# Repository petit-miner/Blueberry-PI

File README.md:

Blueberry PI

I have designed this PCB, because the sheer power of this SoC, at very low power consumption, combined with its display capabilities, it offers options that makers have never seen before.<br> 
<br>
There are two versions available: the 2 layer and 4 layer version.<br> 
Have a look at the subfolder for the 2 and 4 layer version to check out the specific features.<br>
<br>
<br>
The Blueberry PI:<br>
• SoC Allwinner V3s:<br>
	- ARM Cortex-A7 @ 1.2GHz<br>
	- 64 Megabyte of RAM<br>
•	10 / 100M Ethernet <br>
•	Wifi and Bluetooth (RTL8723BS)  <br>
•	1 USB Host Port / 1 micro USB port <br> 
•	MIPI CSI interface<br>
•	pinheader for an OV2640 and an OV7670 parallel camera<br>
•	parallel RGB interface, compatible with 40pin parallel RGB displays<br>
•	audio jack (3,5mm)<br>
•	onboard microphone<br>
•	a 26pin Raspberry PI compatible header<br>
•	SPI Flash <br>
•	SD card slot<br>

The Blueberry PI can boot from an SD card or SPI Flash. <br>
I'm currently <b> not </B> available for custom projects. <br>
If you have any questions email me at info.blueberrypi@gmail.com <br>

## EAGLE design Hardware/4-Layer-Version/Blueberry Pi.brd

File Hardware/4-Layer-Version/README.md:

Hardware

This is the 4 Layer version of the Blueberry PI. It has a richer featureset than the 2 Layer PCB.<br>
Keep in mind that this PCB isn' tested yet, I will keep you updated.<br>
It has the following features:<br>
<br>
• SoC Allwinner V3s:<br>
• ARM Cortex-A7 @ 1.2GHz<br>
• 64 Megabyte of RAM<br>
• Ethernet Jack<br>
• Wifi and Bluetooth (RTL8723BS)<br>
• 1 USB Host Port / 1 micro USB port<br>
• MIPI CSI interface, pin compatible with the Raspberry Pi camera<br>
• pinheader for an OV2640 and an OV7670 parallel camera<br>
• parallel RGB interface, compatible with 40pin parallel RGB displays<br>
• VGA Output<br>
• HDMI Input with the ADV7611 1080p @ 30 fps<br>
• Audio jack (3,5mm)<br>
• onboard microphone<br>
• a 26pin Raspberry PI compatible header<br>
• SPI Flash<br>
• SD card slot <br>
<br>

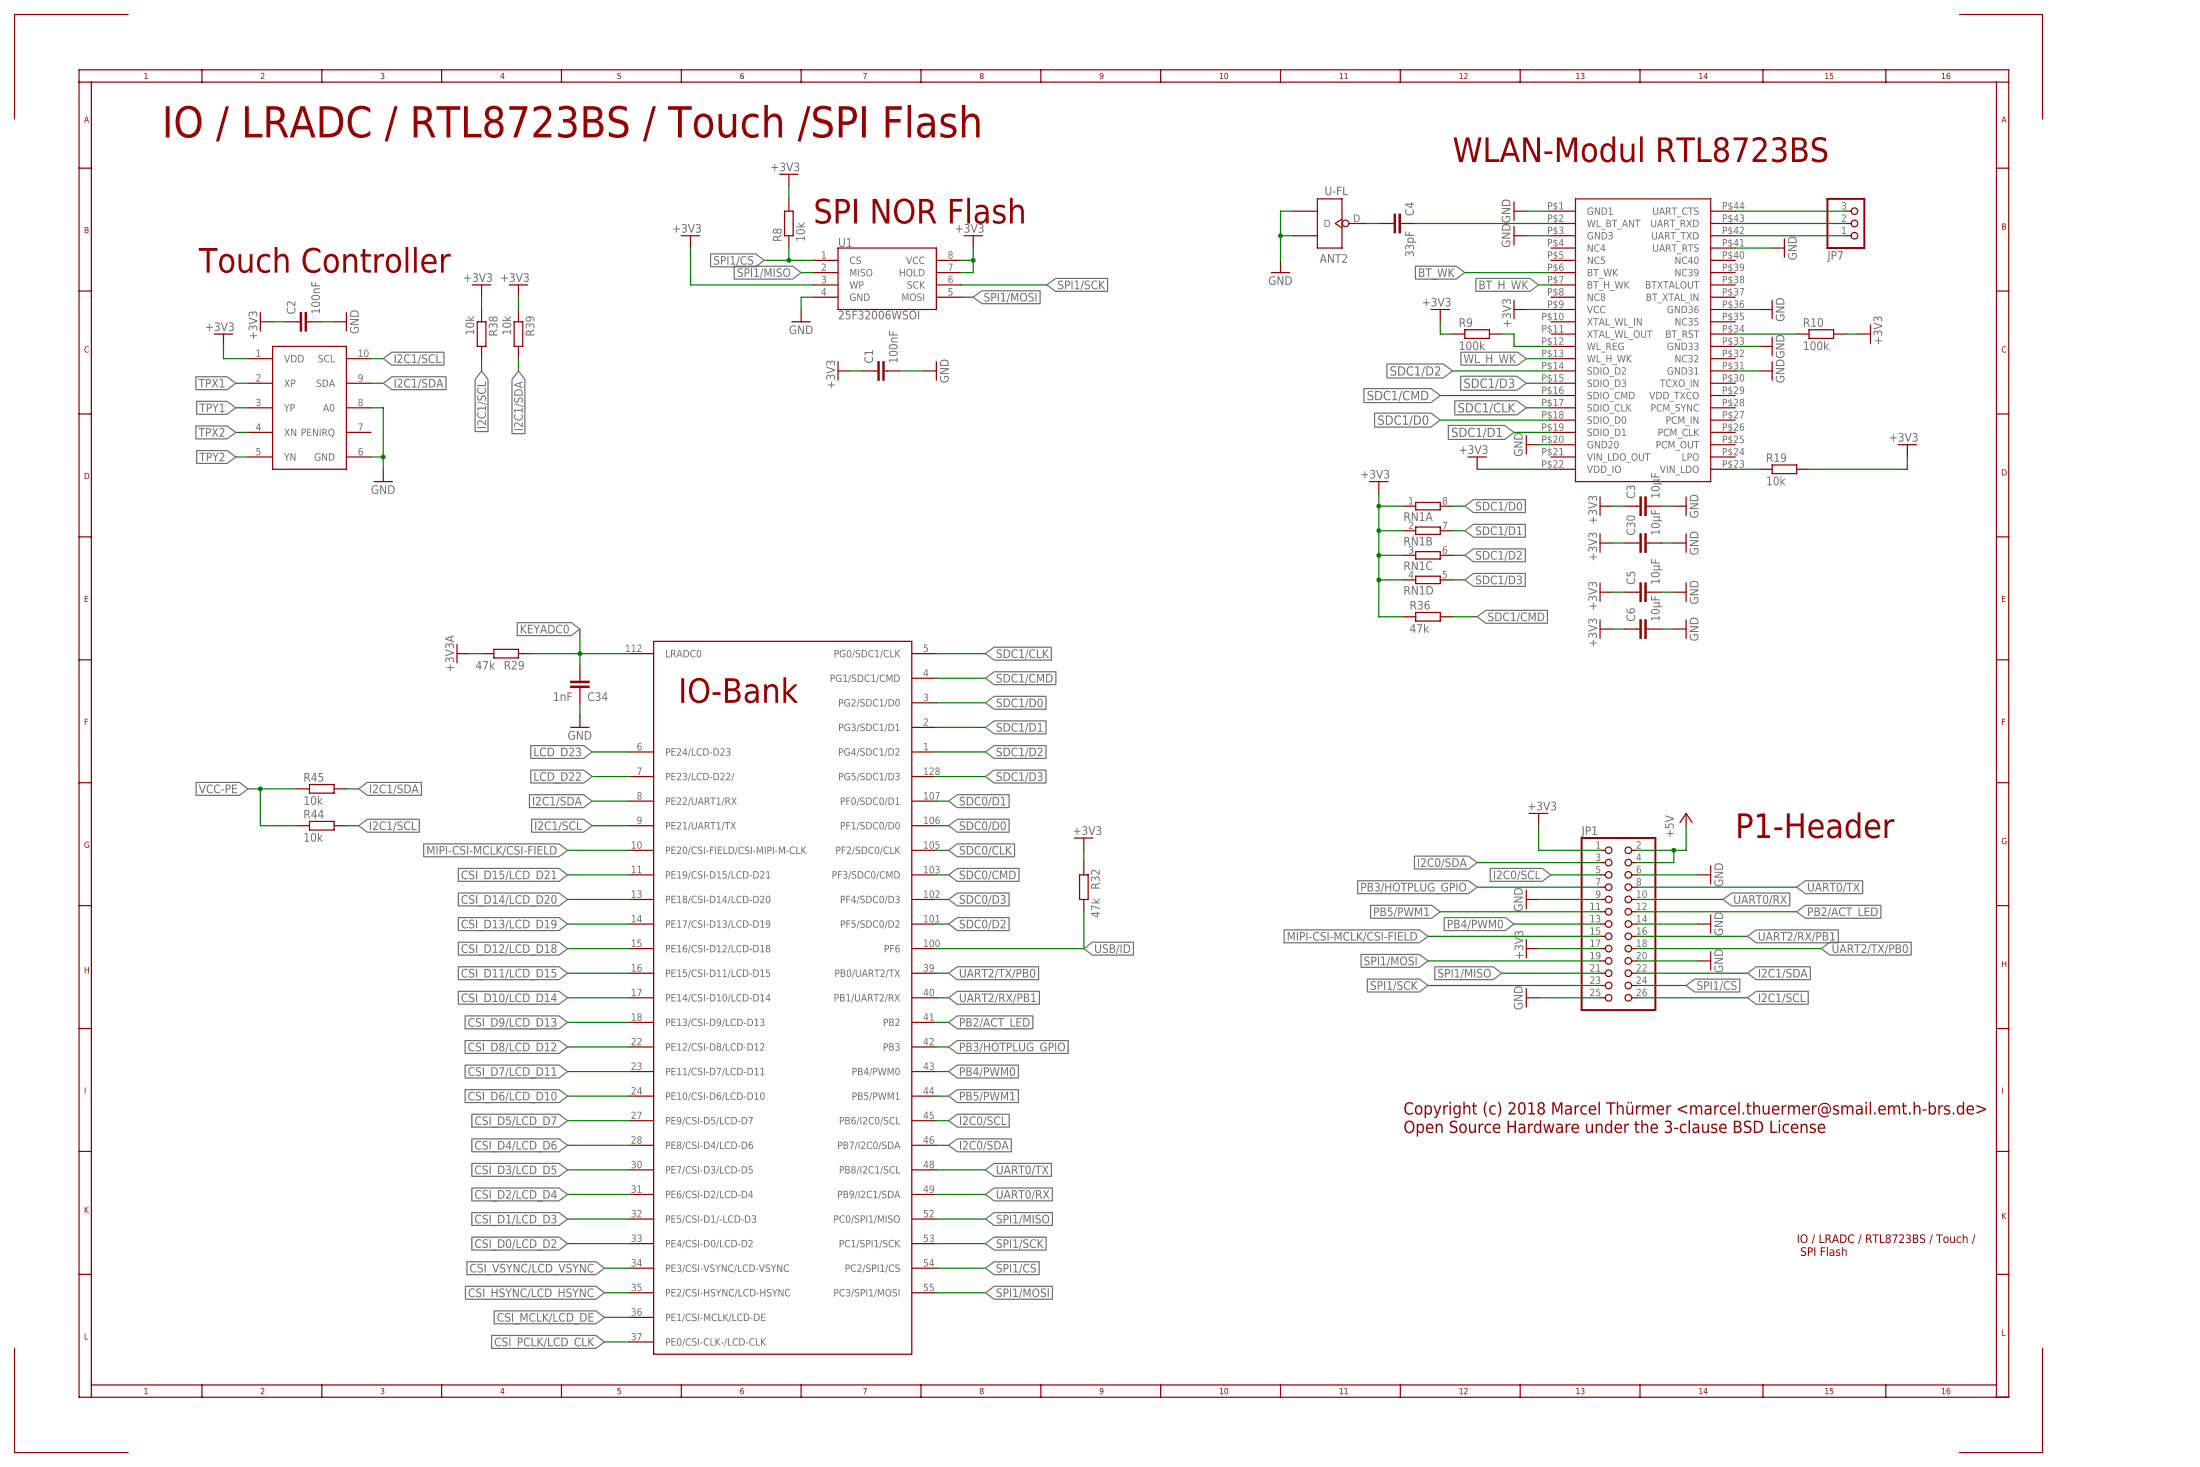
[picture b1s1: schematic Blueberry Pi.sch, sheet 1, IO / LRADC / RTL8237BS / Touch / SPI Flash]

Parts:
ANT2: U-FL; U-FL3P-SMD-2.6X2.6X1.0MM
C1, C2: 100nF; C0603
C3, C5, C6, C30: 10µF; C0805
C4: 33pF; C0603
C34: 1nF; C0603
JP1: PINHD-2X13; 2X13
JP7: PINHD-1X3M; 1X03M
R8, R19, R38, R39, R44, R45: 10k; R0603
R9, R10: 100k; R0603
R29, R32, R36: 47k; R0603
RN1: 4R-NEXB38V; EXB38V
U1: 25F32006WSOI; SO08-EIAJ
U$1: V3S; QFP-128
U$2: RTL8723BS; LGA
U$8: NS2009; MSOP10

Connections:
+3V3: C1.1, C2.1, C3.1, C5.1, C6.1, C30.1, JP1.1, JP1.17, R8.2, R9.1, R10.2, R19.2, R32.1, R36.1, R38.1, R39.1, RN1.1, RN1.2 (1), RN1.3 (1), RN1.4 (1), U1.3 (WP), U1.7 (HOLD), U1.8 (VCC), U$2.P$9 (VCC), U$2.P$22 (VDD_IO), U$8.1 (VDD); also elsewhere on the board
+3V3A: R29.2; also elsewhere on the board
+5V: JP1.2, JP1.4; also elsewhere on the board
BT_H_WK: U$2.P$7 (BT_H_WK)
BT_WK: U$2.P$6 (BT_WK)
CSI_D0/LCD_D2: U$1.33 (PE4/CSI-D0/LCD-D2); also elsewhere on the board
CSI_D1/LCD_D3: U$1.32 (PE5/CSI-D1/-LCD-D3); also elsewhere on the board
CSI_D2/LCD_D4: U$1.31 (PE6/CSI-D2/LCD-D4); also elsewhere on the board
CSI_D3/LCD_D5: U$1.30 (PE7/CSI-D3/LCD-D5); also elsewhere on the board
CSI_D4/LCD_D6: U$1.28 (PE8/CSI-D4/LCD-D6); also elsewhere on the board
CSI_D5/LCD_D7: U$1.27 (PE9/CSI-D5/LCD-D7); also elsewhere on the board
CSI_D6/LCD_D10: U$1.24 (PE10/CSI-D6/LCD-D10); also elsewhere on the board
CSI_D7/LCD_D11: U$1.23 (PE11/CSI-D7/LCD-D11); also elsewhere on the board
CSI_D8/LCD_D12: U$1.22 (PE12/CSI-D8/LCD-D12); also elsewhere on the board
CSI_D9/LCD_D13: U$1.18 (PE13/CSI-D9/LCD-D13); also elsewhere on the board
CSI_D10/LCD_D14: U$1.17 (PE14/CSI-D10/LCD-D14); also elsewhere on the board
CSI_D11/LCD_D15: U$1.16 (PE15/CSI-D11/LCD-D15); also elsewhere on the board
CSI_D12/LCD_D18: U$1.15 (PE16/CSI-D12/LCD-D18); also elsewhere on the board
CSI_D13/LCD_D19: U$1.14 (PE17/CSI-D13/LCD-D19); also elsewhere on the board
CSI_D14/LCD_D20: U$1.13 (PE18/CSI-D14/LCD-D20); also elsewhere on the board
CSI_D15/LCD_D21: U$1.11 (PE19/CSI-D15/LCD-D21); also elsewhere on the board
CSI_HSYNC/LCD_HSYNC: U$1.35 (PE2/CSI-HSYNC/LCD-HSYNC); also elsewhere on the board
CSI_MCLK/LCD_DE: U$1.36 (PE1/CSI-MCLK/LCD-DE); also elsewhere on the board
CSI_PCLK/LCD_CLK: U$1.37 (PE0/CSI-CLK-/LCD-CLK); also elsewhere on the board
CSI_VSYNC/LCD_VSYNC: U$1.34 (PE3/CSI-VSYNC/LCD-VSYNC); also elsewhere on the board
GND: ANT2.GND1, ANT2.GND2, C1.2, C2.2, C3.2, C5.2, C6.2, C30.2, C34.1, JP1.6, JP1.9, JP1.14, JP1.20, JP1.25, U1.4 (GND), U$2.P$1 (GND1), U$2.P$3 (GND3), U$2.P$20 (GND20), U$2.P$31 (GND31), U$2.P$33 (GND33), U$2.P$36 (GND36), U$2.P$41 (UART_RTS), U$8.6 (GND), U$8.8 (A0); also elsewhere on the board
I2C0/SCL: JP1.5, U$1.45 (PB6/I2C0/SCL)
I2C0/SDA: JP1.3, U$1.46 (PB7/I2C0/SDA)
I2C1/SCL: JP1.26, R38.2, R44.2, U$1.9 (PE21/UART1/TX), U$8.10 (SCL); also elsewhere on the board
I2C1/SDA: JP1.22, R39.2, R45.2, U$1.8 (PE22/UART1/RX), U$8.9 (SDA); also elsewhere on the board
KEYADC0: C34.2, R29.1, U$1.112 (LRADC0)
LCD_D22: U$1.7 (PE23/LCD-D22/); also elsewhere on the board
LCD_D23: U$1.6 (PE24/LCD-D23); also elsewhere on the board
MIPI-CSI-MCLK/CSI-FIELD: JP1.15, U$1.10 (PE20/CSI-FIELD/CSI-MIPI-M-CLK); also elsewhere on the board
unnamed: ANT2.D, C4.2
unnamed: R19.1, U$2.P$23 (VIN_LDO)
unnamed: JP7.3, U$2.P$44 (UART_CTS)
unnamed: R9.2, U$2.P$12 (WL_REG)
unnamed: JP7.2, U$2.P$43 (UART_RXD)
unnamed: JP7.1, U$2.P$42 (UART_TXD)
unnamed: R10.1, U$2.P$34 (BT_RST)
unnamed: C4.1, U$2.P$2 (WL_BT_ANT)
PB2/ACT_LED: JP1.12, U$1.41 (PB2); also elsewhere on the board
PB3/HOTPLUG_GPIO: JP1.7, U$1.42 (PB3); also elsewhere on the board
PB4/PWM0: JP1.13, U$1.43 (PB4/PWM0)
PB5/PWM1: JP1.11, U$1.44 (PB5/PWM1)
SDC0/CLK: U$1.105 (PF2/SDC0/CLK); also elsewhere on the board
SDC0/CMD: U$1.103 (PF3/SDC0/CMD); also elsewhere on the board
SDC0/D0: U$1.106 (PF1/SDC0/D0); also elsewhere on the board
SDC0/D1: U$1.107 (PF0/SDC0/D1); also elsewhere on the board
SDC0/D2: U$1.101 (PF5/SDC0/D2); also elsewhere on the board
SDC0/D3: U$1.102 (PF4/SDC0/D3); also elsewhere on the board
SDC1/CLK: U$1.5 (PG0/SDC1/CLK), U$2.P$17 (SDIO_CLK)
SDC1/CMD: R36.2, U$1.4 (PG1/SDC1/CMD), U$2.P$16 (SDIO_CMD)
SDC1/D0: RN1.8 (2), U$1.3 (PG2/SDC1/D0), U$2.P$18 (SDIO_D0)
SDC1/D1: RN1.7 (2), U$1.2 (PG3/SDC1/D1), U$2.P$19 (SDIO_D1)
SDC1/D2: RN1.6 (2), U$1.1 (PG4/SDC1/D2), U$2.P$14 (SDIO_D2)
SDC1/D3: RN1.5 (2), U$1.128 (PG5/SDC1/D3), U$2.P$15 (SDIO_D3)
SPI1/CS: JP1.24, R8.1, U1.1 (CS), U$1.54 (PC2/SPI1/CS)
SPI1/MISO: JP1.21, U1.2 (MISO), U$1.52 (PC0/SPI1/MISO)
SPI1/MOSI: JP1.19, U1.5 (MOSI), U$1.55 (PC3/SPI1/MOSI)
SPI1/SCK: JP1.23, U1.6 (SCK), U$1.53 (PC1/SPI1/SCK)
TPX1: U$8.2 (XP); also elsewhere on the board
TPX2: U$8.4 (XN); also elsewhere on the board
TPY1: U$8.3 (YP); also elsewhere on the board
TPY2: U$8.5 (YN); also elsewhere on the board
UART0/RX: JP1.10, U$1.49 (PB9/I2C1/SDA)
UART0/TX: JP1.8, U$1.48 (PB8/I2C1/SCL)
UART2/RX/PB1: JP1.16, U$1.40 (PB1/UART2/RX)
UART2/TX/PB0: JP1.18, U$1.39 (PB0/UART2/TX)
USB/ID: R32.2, U$1.100 (PF6); also elsewhere on the board
VCC-PE: R44.1, R45.1; also elsewhere on the board
WL_H_WK: U$2.P$13 (WL_H_WK)

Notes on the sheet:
IO / LRADC / RTL8723BS / Touch / SPI Flash
Copyright (c) 2018 Marcel Thürmer <marcel.thuermer@smail.emt.h-brs.de> Open Source Hardware under the 3-clause BSD License
SPI NOR Flash
WLAN-Modul RTL8723BS
P1-Header
Touch Controller
IO / LRADC / RTL8723BS / Touch /SPI Flash

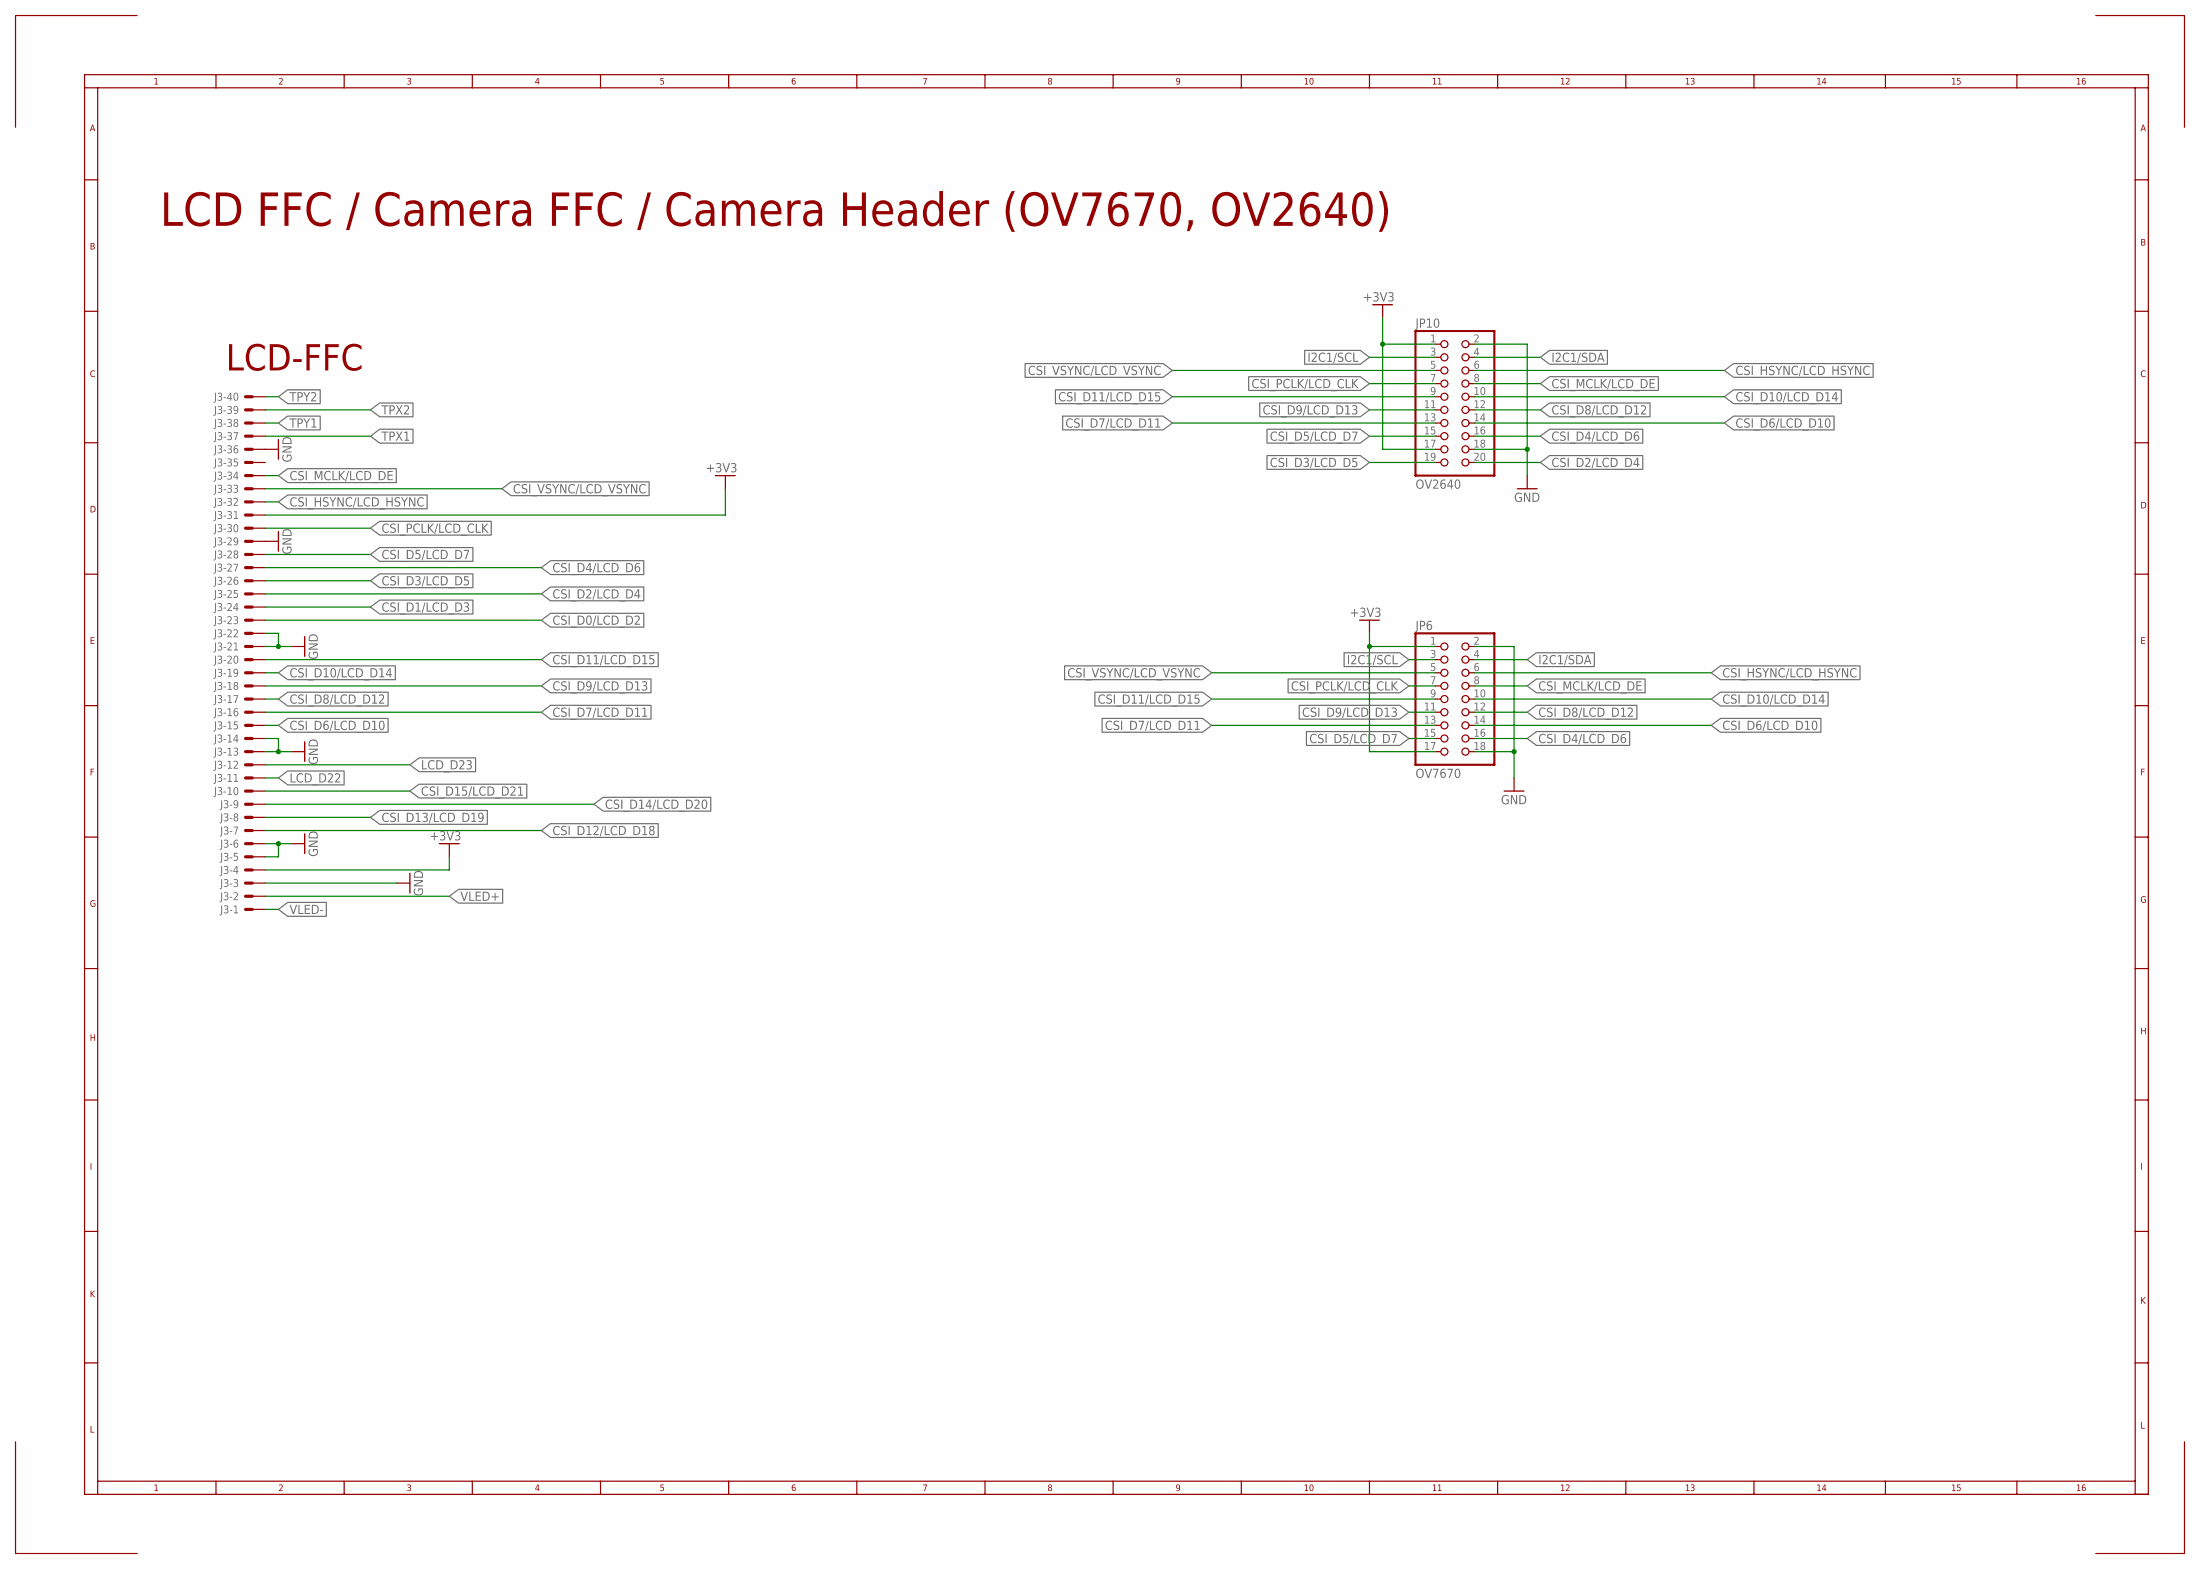
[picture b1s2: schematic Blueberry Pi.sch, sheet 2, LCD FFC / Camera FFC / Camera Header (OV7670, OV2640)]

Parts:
J3: 40PINFPCH15-1LW; XF2H-4015-1LW
JP6: OV7670; 2X09
JP10: OV2640; 2X10

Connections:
+3V3: J3.4 (MS), J3.31 (MS), JP6.1, JP6.17, JP10.1, JP10.17; also elsewhere on the board
CSI_D0/LCD_D2: J3.23 (MS); also elsewhere on the board
CSI_D1/LCD_D3: J3.24 (MS); also elsewhere on the board
CSI_D2/LCD_D4: J3.25 (MS), JP10.20; also elsewhere on the board
CSI_D3/LCD_D5: J3.26 (MS), JP10.19; also elsewhere on the board
CSI_D4/LCD_D6: J3.27 (MS), JP6.16, JP10.16; also elsewhere on the board
CSI_D5/LCD_D7: J3.28 (MS), JP6.15, JP10.15; also elsewhere on the board
CSI_D6/LCD_D10: J3.15 (MS), JP6.14, JP10.14; also elsewhere on the board
CSI_D7/LCD_D11: J3.16 (MS), JP6.13, JP10.13; also elsewhere on the board
CSI_D8/LCD_D12: J3.17 (MS), JP6.12, JP10.12; also elsewhere on the board
CSI_D9/LCD_D13: J3.18 (MS), JP6.11, JP10.11; also elsewhere on the board
CSI_D10/LCD_D14: J3.19 (MS), JP6.10, JP10.10; also elsewhere on the board
CSI_D11/LCD_D15: J3.20 (MS), JP6.9, JP10.9; also elsewhere on the board
CSI_D12/LCD_D18: J3.7 (MS); also elsewhere on the board
CSI_D13/LCD_D19: J3.8 (MS); also elsewhere on the board
CSI_D14/LCD_D20: J3.9 (MS); also elsewhere on the board
CSI_D15/LCD_D21: J3.10 (MS); also elsewhere on the board
CSI_HSYNC/LCD_HSYNC: J3.32 (MS), JP6.6, JP10.6; also elsewhere on the board
CSI_MCLK/LCD_DE: J3.34 (MS), JP6.8, JP10.8; also elsewhere on the board
CSI_PCLK/LCD_CLK: J3.30 (MS), JP6.7, JP10.7; also elsewhere on the board
CSI_VSYNC/LCD_VSYNC: J3.33 (MS), JP6.5, JP10.5; also elsewhere on the board
GND: J3.3 (MS), J3.5 (MS), J3.6 (MS), J3.13 (MS), J3.14 (MS), J3.21 (MS), J3.22 (MS), J3.29 (MS), J3.36 (MS), JP6.2, JP6.18, JP10.2, JP10.18; also elsewhere on the board
I2C1/SCL: JP6.3, JP10.3; also elsewhere on the board
I2C1/SDA: JP6.4, JP10.4; also elsewhere on the board
LCD_D22: J3.11 (MS); also elsewhere on the board
LCD_D23: J3.12 (MS); also elsewhere on the board
TPX1: J3.37 (MS); also elsewhere on the board
TPX2: J3.39 (MS); also elsewhere on the board
TPY1: J3.38 (MS); also elsewhere on the board
TPY2: J3.40 (MS); also elsewhere on the board
VLED+: J3.2 (MS); also elsewhere on the board
VLED-: J3.1 (MSV); also elsewhere on the board

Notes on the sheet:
LCD-FFC
LCD FFC / Camera FFC / Camera Header (OV7670, OV2640)

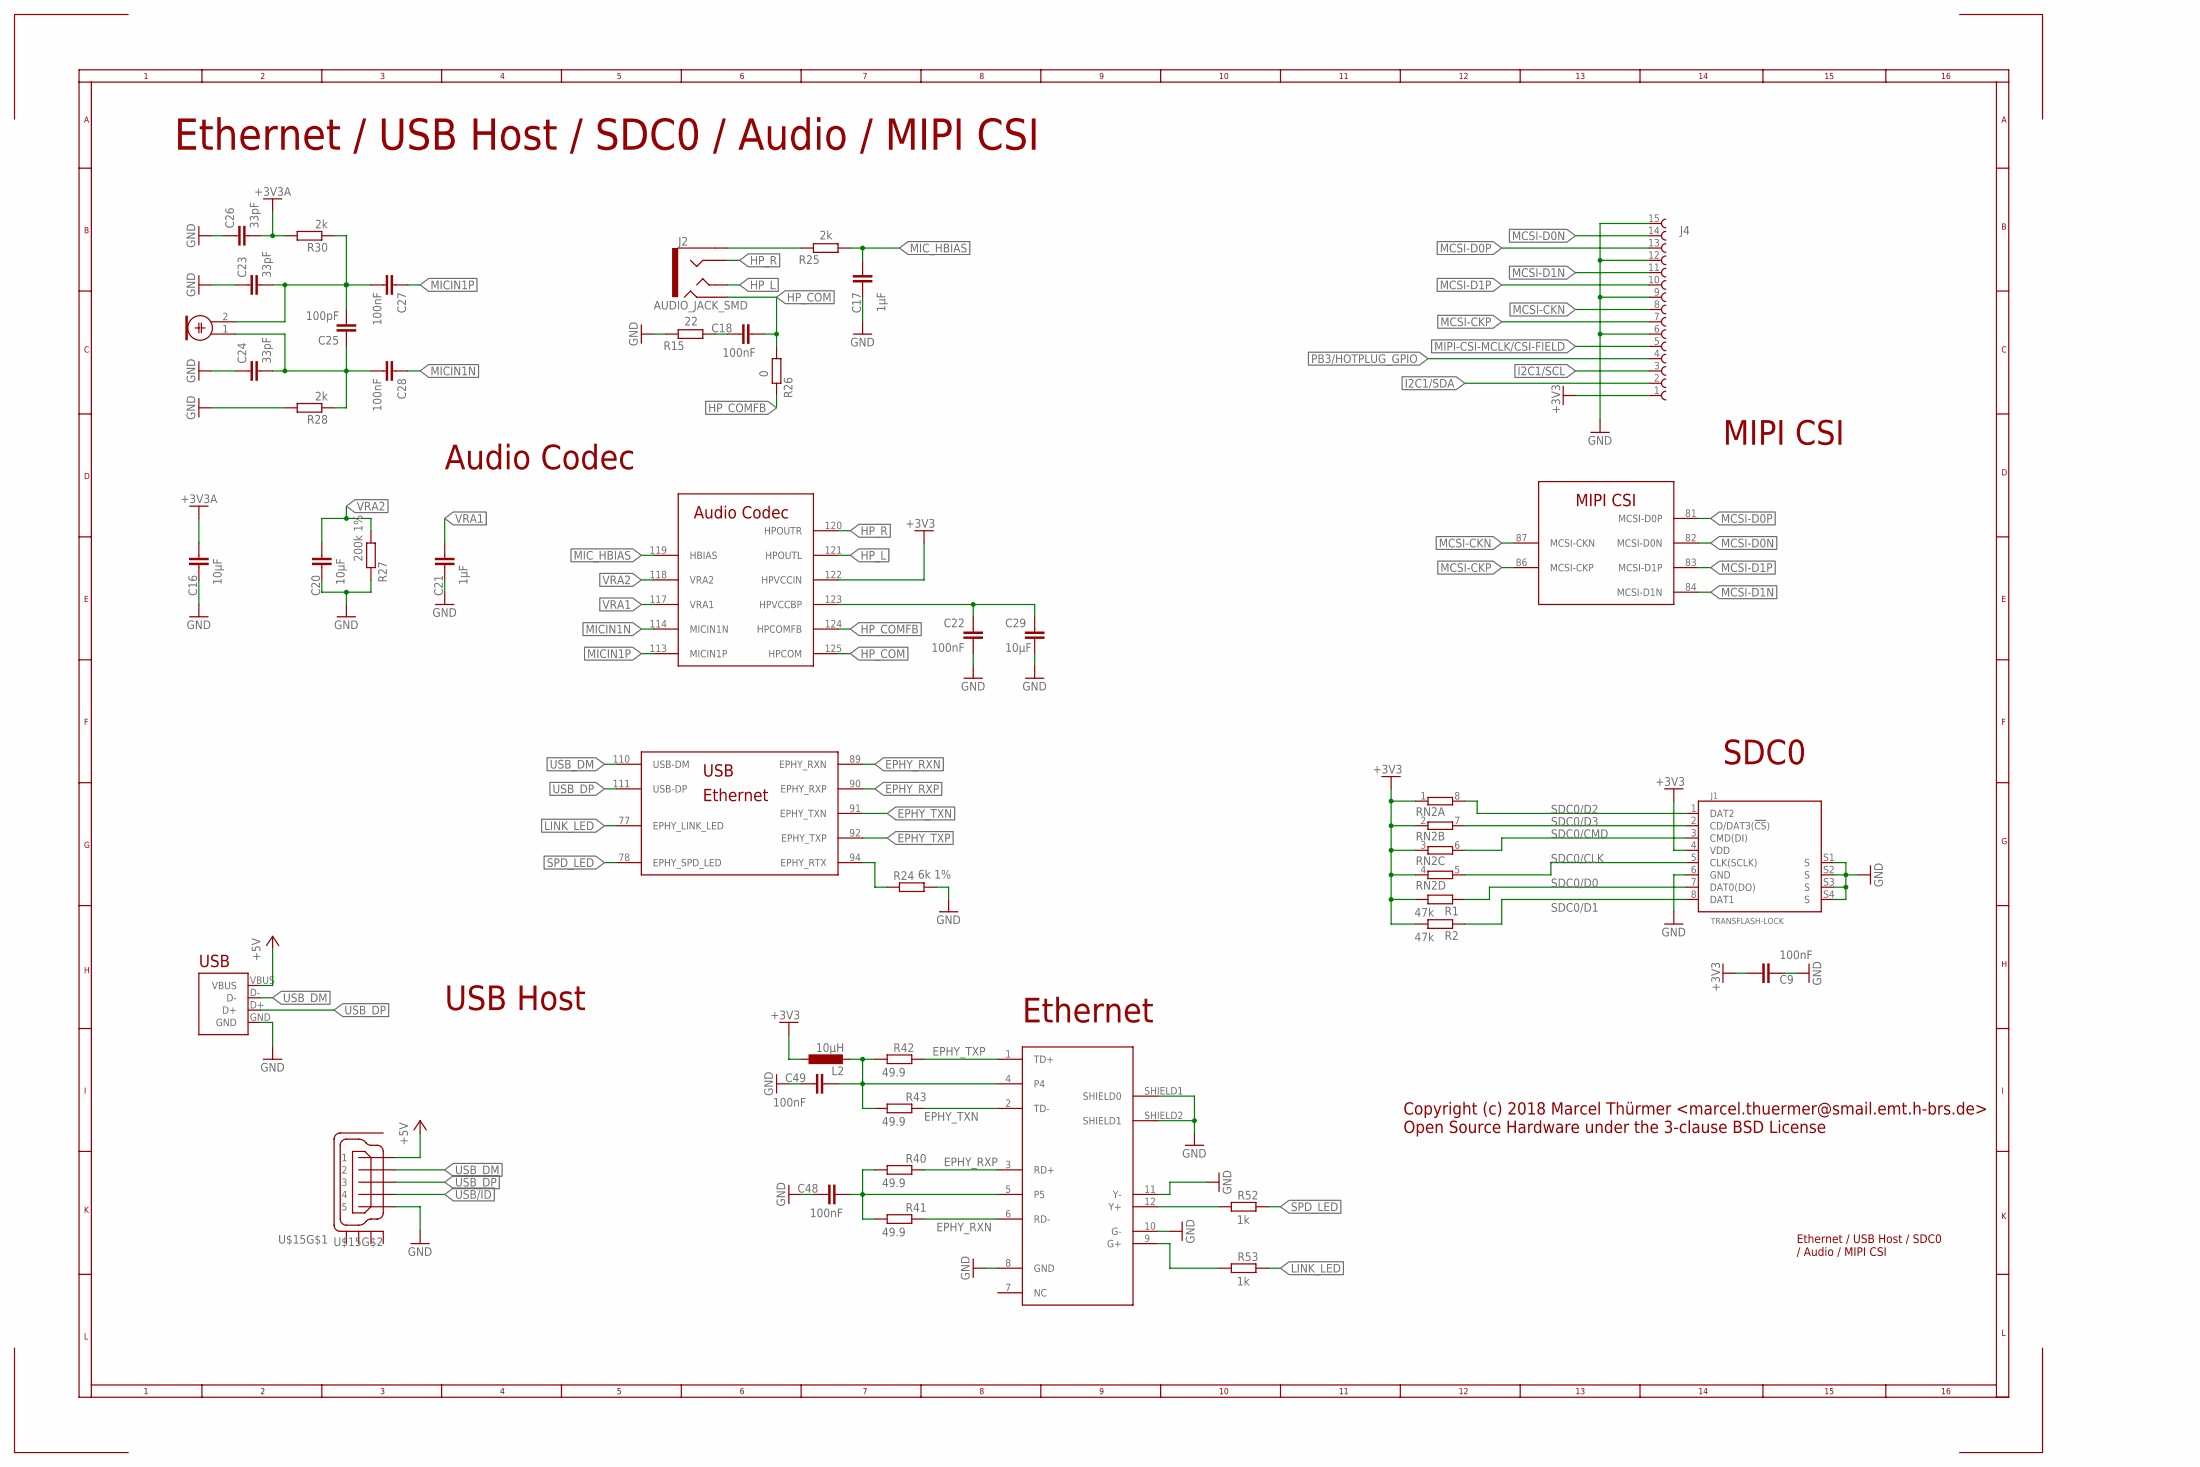
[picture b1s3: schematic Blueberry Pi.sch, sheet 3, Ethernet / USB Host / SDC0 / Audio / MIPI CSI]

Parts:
C9, C18, C22, C27, C28, C48, C49: 100nF; C0603
C16, C20, C29: 10µF; C0805
C17, C21: 1µF; C0603
C23, C24, C26: 33pF; C0603
C25: 100pF; C0603
J1: TRANSFLASH-LOCK; TRANSFLASH-LOCK-SOCK
J2: AUDIO_JACK_SMD; AUDIO_JACK_3.5MM_TRRS_SMD_RA
J4: 68611514122
L2: 10µH; L0805
MIC: ELECTRET_MICROPHON-F6035AP; F6035AP
R1, R2: 47k; R0603
R15: 22; R0603
R24: 6k 1%; R0603
R25, R28, R30: 2k; R0603
R26: 0; R0603
R27: 200k 1%; R0603
R40, R41, R42, R43: 49.9; R0603
R52, R53: 1k; R0603
RN2: 4R-NEXB38V; EXB38V
U$1: V3S; QFP-128
U$3: HR911105A; RJ45
U$15: CON-HIROSE_MICRO-USB-SHIELD-ZX62R-B-5P; CON-HIROSE_ZX62R-B-5P
X1: USB-B-S; USB-B-SMT

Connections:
+3V3: C9.1, J1.4 (VDD), J4.1 (15), L2.1, R1.2, R2.2, RN2.1, RN2.2 (1), RN2.3 (1), RN2.4 (1), U$1.122 (HPVCCIN); also elsewhere on the board
+3V3A: C16.2, C26.2, R30.2; also elsewhere on the board
+5V: U$15.1, X1.VBUS; also elsewhere on the board
EPHY_RXN: R41.1, U$1.89 (EPHY_RXN), U$3.6 (RD-)
EPHY_RXP: R40.1, U$1.90 (EPHY_RXP), U$3.3 (RD+)
EPHY_TXN: R43.1, U$1.91 (EPHY_TXN), U$3.2 (TD-)
EPHY_TXP: R42.1, U$1.92 (EPHY_TXP), U$3.1 (TD+)
GND: C9.2, C16.1, C17.2, C20.1, C21.1, C22.2, C23.1, C24.1, C26.1, C29.1, C48.2, C49.2, J1.6 (GND), J1.S1 (S), J1.S2 (S), J1.S3 (S), J1.S4 (S), J4.6 (10), J4.9 (7), J4.12 (4), J4.15 (1), R15.1, R24.2, R27.1, R28.2, U$3.8 (GND), U$3.10 (G-), U$3.11 (Y-), U$3.SHIELD1 (SHIELD0), U$3.SHIELD2 (SHIELD1), U$15.5, X1.GND; also elsewhere on the board
HP_COM: C18.2, J2.RING2, R26.2, U$1.125 (HPCOM)
HP_COMFB: R26.1, U$1.124 (HPCOMFB)
HP_L: J2.TIP, U$1.121 (HPOUTL)
HP_R: J2.RING1, U$1.120 (HPOUTR)
I2C1/SCL: J4.3 (13); also elsewhere on the board
I2C1/SDA: J4.2 (14); also elsewhere on the board
LINK_LED: R53.1, U$1.77 (EPHY_LINK_LED)
MCSI-CKN: J4.8, U$1.87 (MCSI-CKN)
MCSI-CKP: J4.7 (9), U$1.86 (MCSI-CKP)
MCSI-D0N: J4.14 (2), U$1.82 (MCSI-D0N)
MCSI-D0P: J4.13 (3), U$1.81 (MCSI-D0P)
MCSI-D1N: J4.11 (5), U$1.84 (MCSI-D1N)
MCSI-D1P: J4.10 (6), U$1.83 (MCSI-D1P)
MICIN1N: C28.1, U$1.114 (MICIN1N)
MICIN1P: C27.1, U$1.113 (MICIN1P)
MIC_HBIAS: C17.1, R25.2, U$1.119 (HBIAS)
MIPI-CSI-MCLK/CSI-FIELD: J4.5 (11); also elsewhere on the board
unnamed: R24.1, U$1.94 (EPHY_RTX)
unnamed: R53.2, U$3.9 (G+)
unnamed: R52.2, U$3.12 (Y+)
unnamed: C49.1, L2.2, R42.2, R43.2, U$3.4
unnamed: C48.1, R40.2, R41.2, U$3.5
unnamed: C22.1, C29.2, U$1.123 (HPVCCBP)
unnamed: J2.EARTH, R25.1
unnamed: C18.1, R15.2
unnamed: C23.2, C25.2, C27.2, MIC.2, R30.1
unnamed: C24.2, C25.1, C28.2, MIC.1, R28.1
PB3/HOTPLUG_GPIO: J4.4 (12); also elsewhere on the board
SDC0/CLK: J1.5 (CLK(SCLK)), RN2.5 (2); also elsewhere on the board
SDC0/CMD: J1.3 (CMD(DI)), RN2.6 (2); also elsewhere on the board
SDC0/D0: J1.7 (DAT0(DO)), R1.1; also elsewhere on the board
SDC0/D1: J1.8 (DAT1), R2.1; also elsewhere on the board
SDC0/D2: J1.1 (DAT2), RN2.8 (2); also elsewhere on the board
SDC0/D3: J1.2 (CD/DAT3(!CS!)), RN2.7 (2); also elsewhere on the board
SPD_LED: R52.1, U$1.78 (EPHY_SPD_LED)
USB/ID: U$15.4; also elsewhere on the board
USB_DM: U$1.110 (USB-DM), U$15.2, X1.D-
USB_DP: U$1.111 (USB-DP), U$15.3, X1.D+
VRA1: C21.2, U$1.117 (VRA1)
VRA2: C20.2, R27.2, U$1.118 (VRA2)

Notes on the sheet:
Ethernet / USB Host / SDC0 / Audio / MIPI CSI
USB Host
Audio Codec
MIPI CSI
Ethernet
SDC0
Copyright (c) 2018 Marcel Thürmer <marcel.thuermer@smail.emt.h-brs.de> Open Source Hardware under the 3-clause BSD License
Ethernet / USB Host / SDC0 / Audio / MIPI CSI

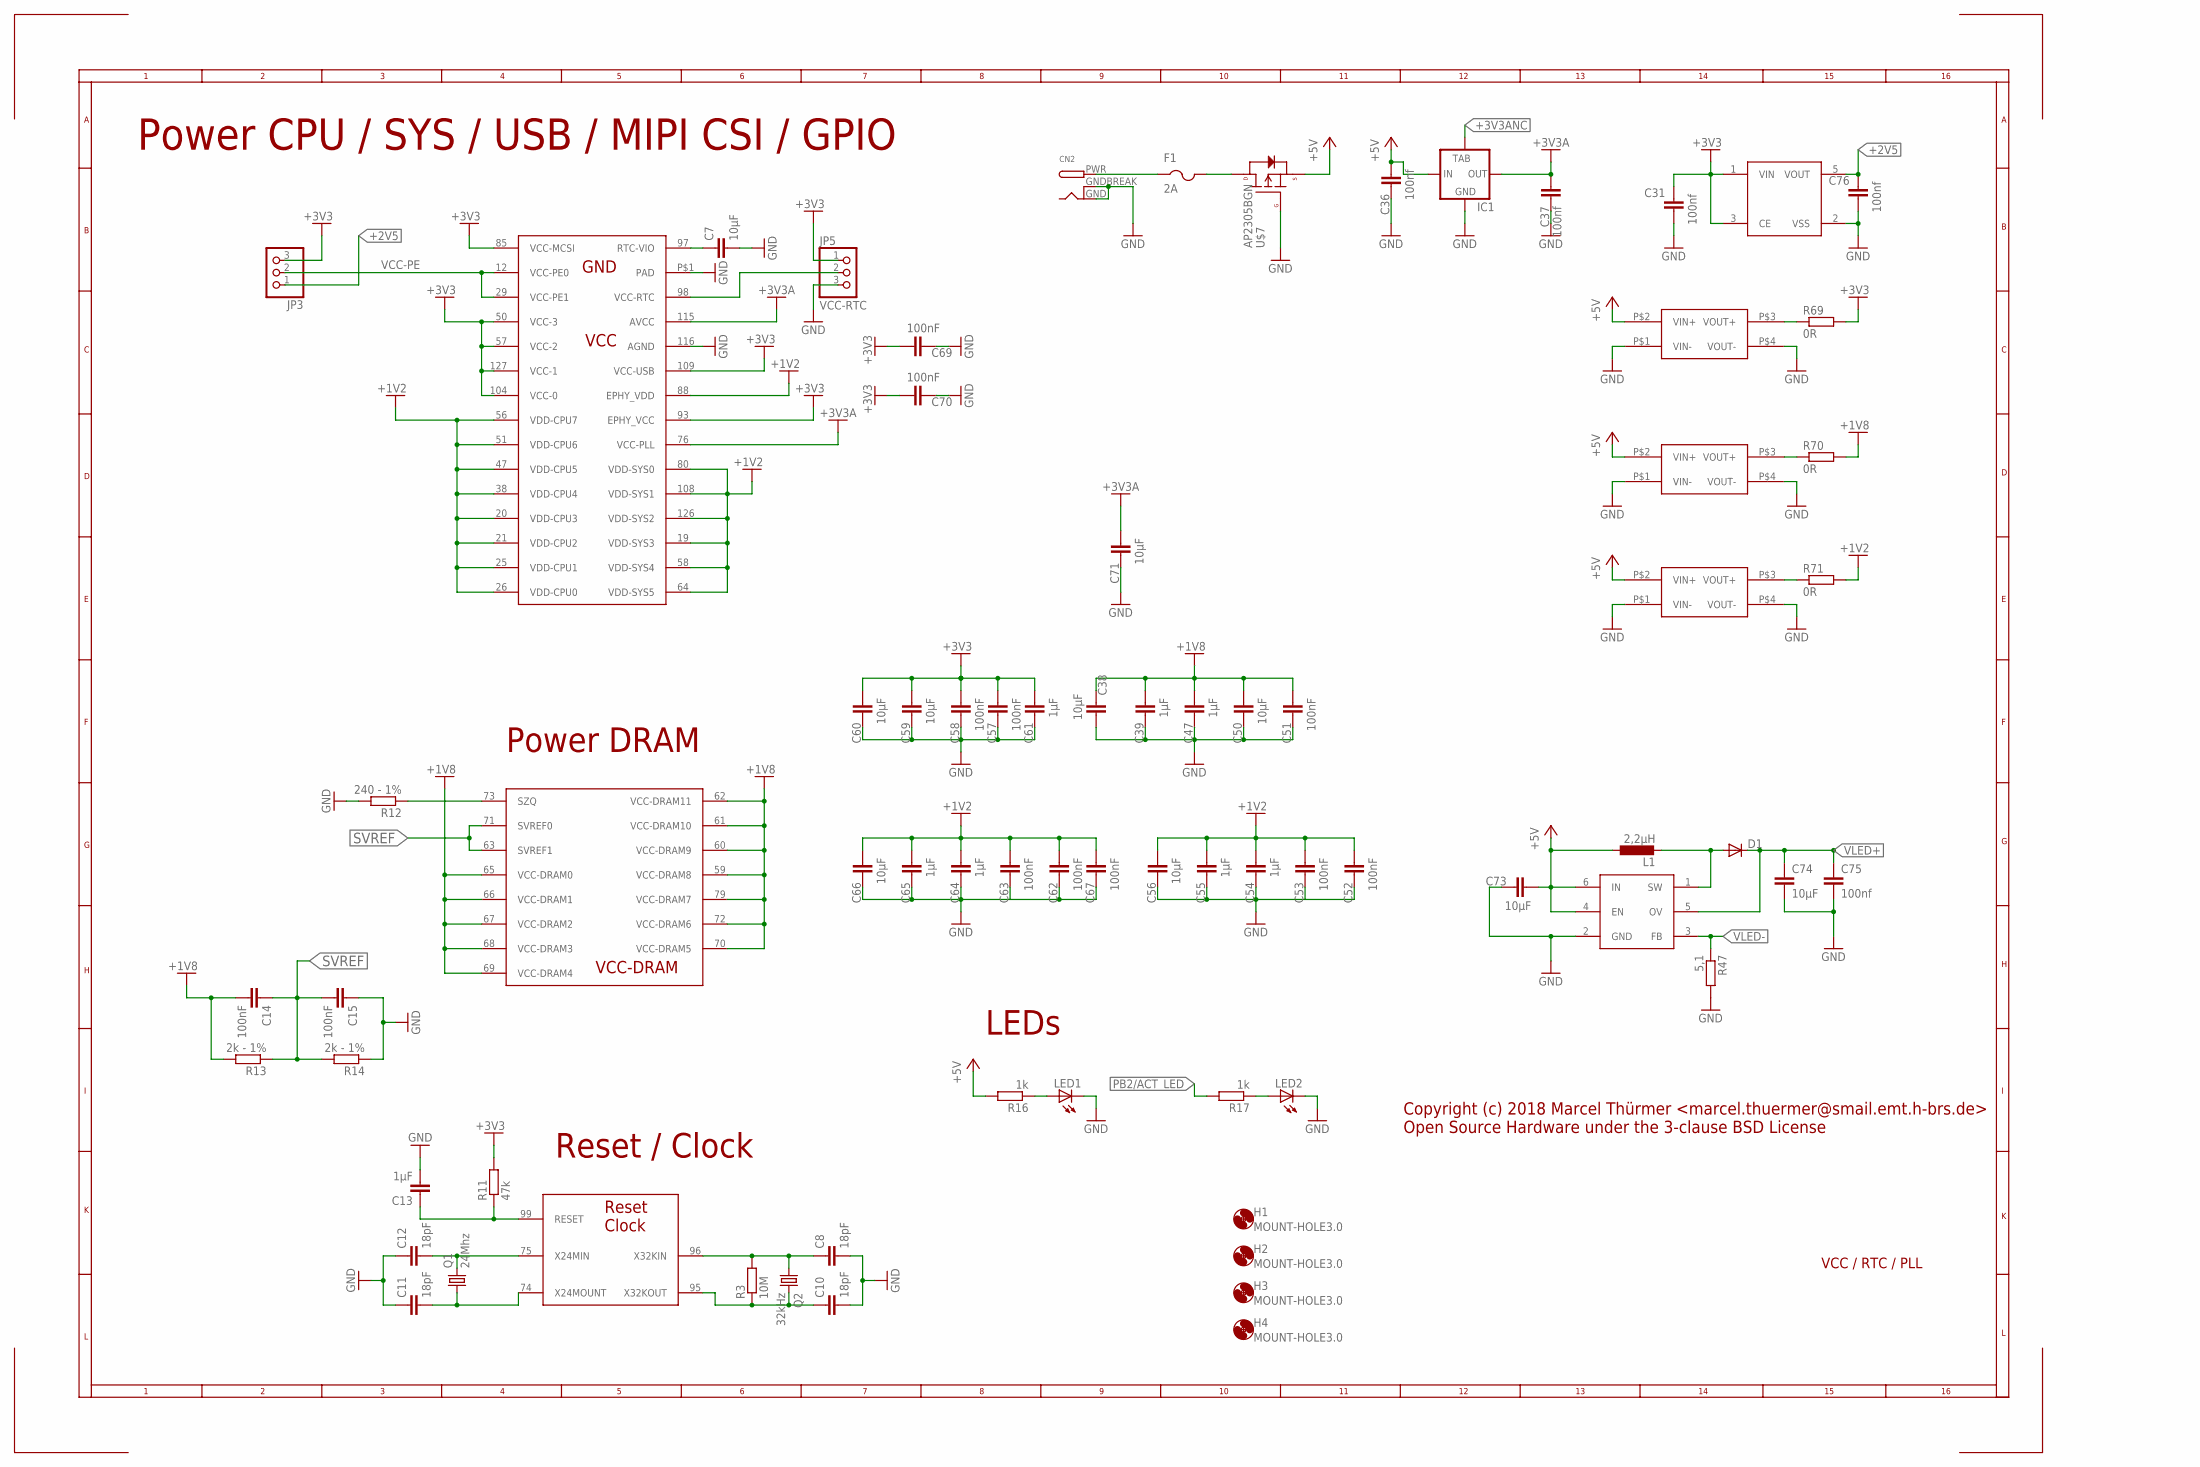
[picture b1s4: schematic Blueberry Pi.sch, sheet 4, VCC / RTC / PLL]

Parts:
C7, C50, C59, C66, C73, C74: 10µF; C0805
C8, C10, C11, C12: 18pF; C0603
C13, C39, C47, C55, C64, C65: 1µF; C0603
C14, C15, C51, C53, C57, C58, C62, C67, C70: 100nF; C0603
C31, C36, C37, C75, C76: 100nf; C0603
C38, C56, C60, C71: 10µF; C0603
C52, C63, C69: 100nF; C0805
C54, C61: 1µF; C0805
CN2: DCBARRELPTH; DCJACK_2MM_PTH
D1: DIODE-SOD323-W; SOD323-W
F1: 2A; R1206
H1, H2, H3, H4: MOUNT-HOLE3.0; 3,0
IC1: LM1117; SOT223
JP3: PINHD-1X3; 1X03
JP5: VCC-RTC; 1X03
L1: 2,2µH; ODD-INDUCTOR
LED1, LED2: LEDCHIPLED_0805; CHIPLED_0805
Q1: 24Mhz; HC49U-V
Q2: 32kHz; TC38H
R3: 10M; R0603
R11: 47k; R0603
R12: 240 - 1%; R0603
R13, R14: 2k - 1%; R0603
R16, R17: 1k; R0603
R47: 5,1; R0603
R69, R70, R71: 0R; R0603
U$1: V3S; QFP-128
U$4, U$10, U$11: MP1584-MINI; MINI-DC-BRICK
U$6: XC6204; SOT25
U$7: AP2305BGN; SOT23-3
U$9: PT4101; SOT23-6

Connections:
5VNS: CN2.PWR, F1.1
+1V2: C52.1, C53.1, C54.1, C55.1, C56.1, C62.1, C63.1, C64.1, C65.1, C66.1, C67.1, R71.2, U$1.19 (VDD-SYS3), U$1.20 (VDD-CPU3), U$1.21 (VDD-CPU2), U$1.25 (VDD-CPU1), U$1.26 (VDD-CPU0), U$1.38 (VDD-CPU4), U$1.47 (VDD-CPU5), U$1.51 (VDD-CPU6), U$1.56 (VDD-CPU7), U$1.58 (VDD-SYS4), U$1.64 (VDD-SYS5), U$1.80 (VDD-SYS0), U$1.88 (EPHY_VDD), U$1.108 (VDD-SYS1), U$1.126 (VDD-SYS2)
+1V8: C14.2, C38.2, C39.1, C47.1, C50.1, C51.1, R13.2, R70.2, U$1.59 (VCC-DRAM8), U$1.60 (VCC-DRAM9), U$1.61 (VCC-DRAM10), U$1.62 (VCC-DRAM11), U$1.65 (VCC-DRAM0), U$1.66 (VCC-DRAM1), U$1.67 (VCC-DRAM2), U$1.68 (VCC-DRAM3), U$1.69 (VCC-DRAM4), U$1.70 (VCC-DRAM5), U$1.72 (VCC-DRAM6), U$1.79 (VCC-DRAM7)
+2V5: C76.1, JP3.1, U$6.5 (VOUT)
+3V3: C31.1, C57.1, C58.1, C59.1, C60.1, C61.1, C69.1, C70.1, JP3.3, JP5.1, R11.2, R69.2, U$1.50 (VCC-3), U$1.57 (VCC-2), U$1.85 (VCC-MCSI), U$1.93 (EPHY_VCC), U$1.104 (VCC-0), U$1.109 (VCC-USB), U$1.127 (VCC-1), U$6.1 (VIN), U$6.3 (CE); also elsewhere on the board
+3V3A: C37.1, C71.1, IC1.2 (OUT), U$1.76 (VCC-PLL), U$1.115 (AVCC); also elsewhere on the board
+3V3ANC: IC1.4 (IN1)
+5V: C36.1, C73.1, IC1.3 (IN), L1.P$1 (1), R16.2, U$4.P$2 (VIN+), U$7.2 (S), U$9.4 (EN), U$9.6 (IN), U$10.P$2 (VIN+), U$11.P$2 (VIN+); also elsewhere on the board
GND: C7.2, C8.2, C10.2, C11.1, C12.1, C13.2, C15.1, C31.2, C36.2, C37.2, C38.1, C39.2, C47.2, C50.2, C51.2, C52.2, C53.2, C54.2, C55.2, C56.2, C57.2, C58.2, C59.2, C60.2, C61.2, C62.2, C63.2, C64.2, C65.2, C66.2, C67.2, C69.2, C70.2, C71.2, C73.2, C74.2, C75.2, C76.2, CN2.GND, CN2.GNDBREAK, IC1.1 (GND), JP5.3, LED1.C, LED2.C, R12.2, R14.1, R47.2, U$1.116 (AGND), U$1.P$1 (PAD), U$4.P$1 (VIN-), U$4.P$4 (VOUT-), U$6.2 (VSS), U$7.1 (G), U$9.2 (GND), U$10.P$1 (VIN-), U$10.P$4 (VOUT-), U$11.P$1 (VIN-), U$11.P$4 (VOUT-); also elsewhere on the board
unnamed: LED1.A, R16.1
unnamed: LED2.A, R17.1
unnamed: D1.A, L1.P$2 (2), U$9.1 (SW)
unnamed: C7.1, U$1.97 (RTC-VIO)
unnamed: JP5.2, U$1.98 (VCC-RTC)
unnamed: C10.1, Q2.2, R3.1, U$1.95 (X32KOUT)
unnamed: C8.1, Q2.1, R3.2, U$1.96 (X32KIN)
unnamed: C11.2, Q1.1, U$1.74 (X24MOUNT)
unnamed: C12.2, Q1.2, U$1.75 (X24MIN)
unnamed: C13.1, R11.1, U$1.99 (RESET)
unnamed: R12.1, U$1.73 (SZQ)
unnamed: R69.1, U$4.P$3 (VOUT+)
unnamed: R70.1, U$10.P$3 (VOUT+)
unnamed: F1.2, U$7.3 (D)
unnamed: R71.1, U$11.P$3 (VOUT+)
PB2/ACT_LED: R17.2; also elsewhere on the board
SVREF: C14.1, C15.2, R13.1, R14.2, U$1.63 (SVREF1), U$1.71 (SVREF0)
VCC-PE: JP3.2, U$1.12 (VCC-PE0), U$1.29 (VCC-PE1); also elsewhere on the board
VLED+: C74.1, C75.1, D1.C, U$9.5 (OV); also elsewhere on the board
VLED-: R47.1, U$9.3 (FB); also elsewhere on the board

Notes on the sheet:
VCC / RTC / PLL
Power CPU / SYS / USB / MIPI CSI / GPIO
Power DRAM
Copyright (c) 2018 Marcel Thürmer <marcel.thuermer@smail.emt.h-brs.de> Open Source Hardware under the 3-clause BSD License
Reset / Clock
LEDs

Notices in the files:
parts and their libraries:
supply0: Copyright (C) 2007, Bob Starr
SparkFun-Switches: Licensing: Creative Commons ShareAlike 4.0 International - https://creativecommons.org/licenses/by-sa/4.0
EAGLE-FPC_CONNECTOR_AND_FFC_CAB-rev16b: Copyright: Würth Elektronik
